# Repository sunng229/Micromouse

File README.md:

## Micromouse

An autonomous maze solving robot for the IEEE club at UCLA. The goal is to build and design a robot that autonomously navigates through a 16x16 maze to reach the center and back as fast as possible.

It accomplishes this using IR sensors to detect any walls, continously storing that data as it continues its path primarily using an algorithm called Floodfill, which is implemented in solver.c inside the Src folder.

Included are the following:
* Src folder: all the important source code  
* Inc folder: the H files for the C files
* the build/schematic files for the PCB

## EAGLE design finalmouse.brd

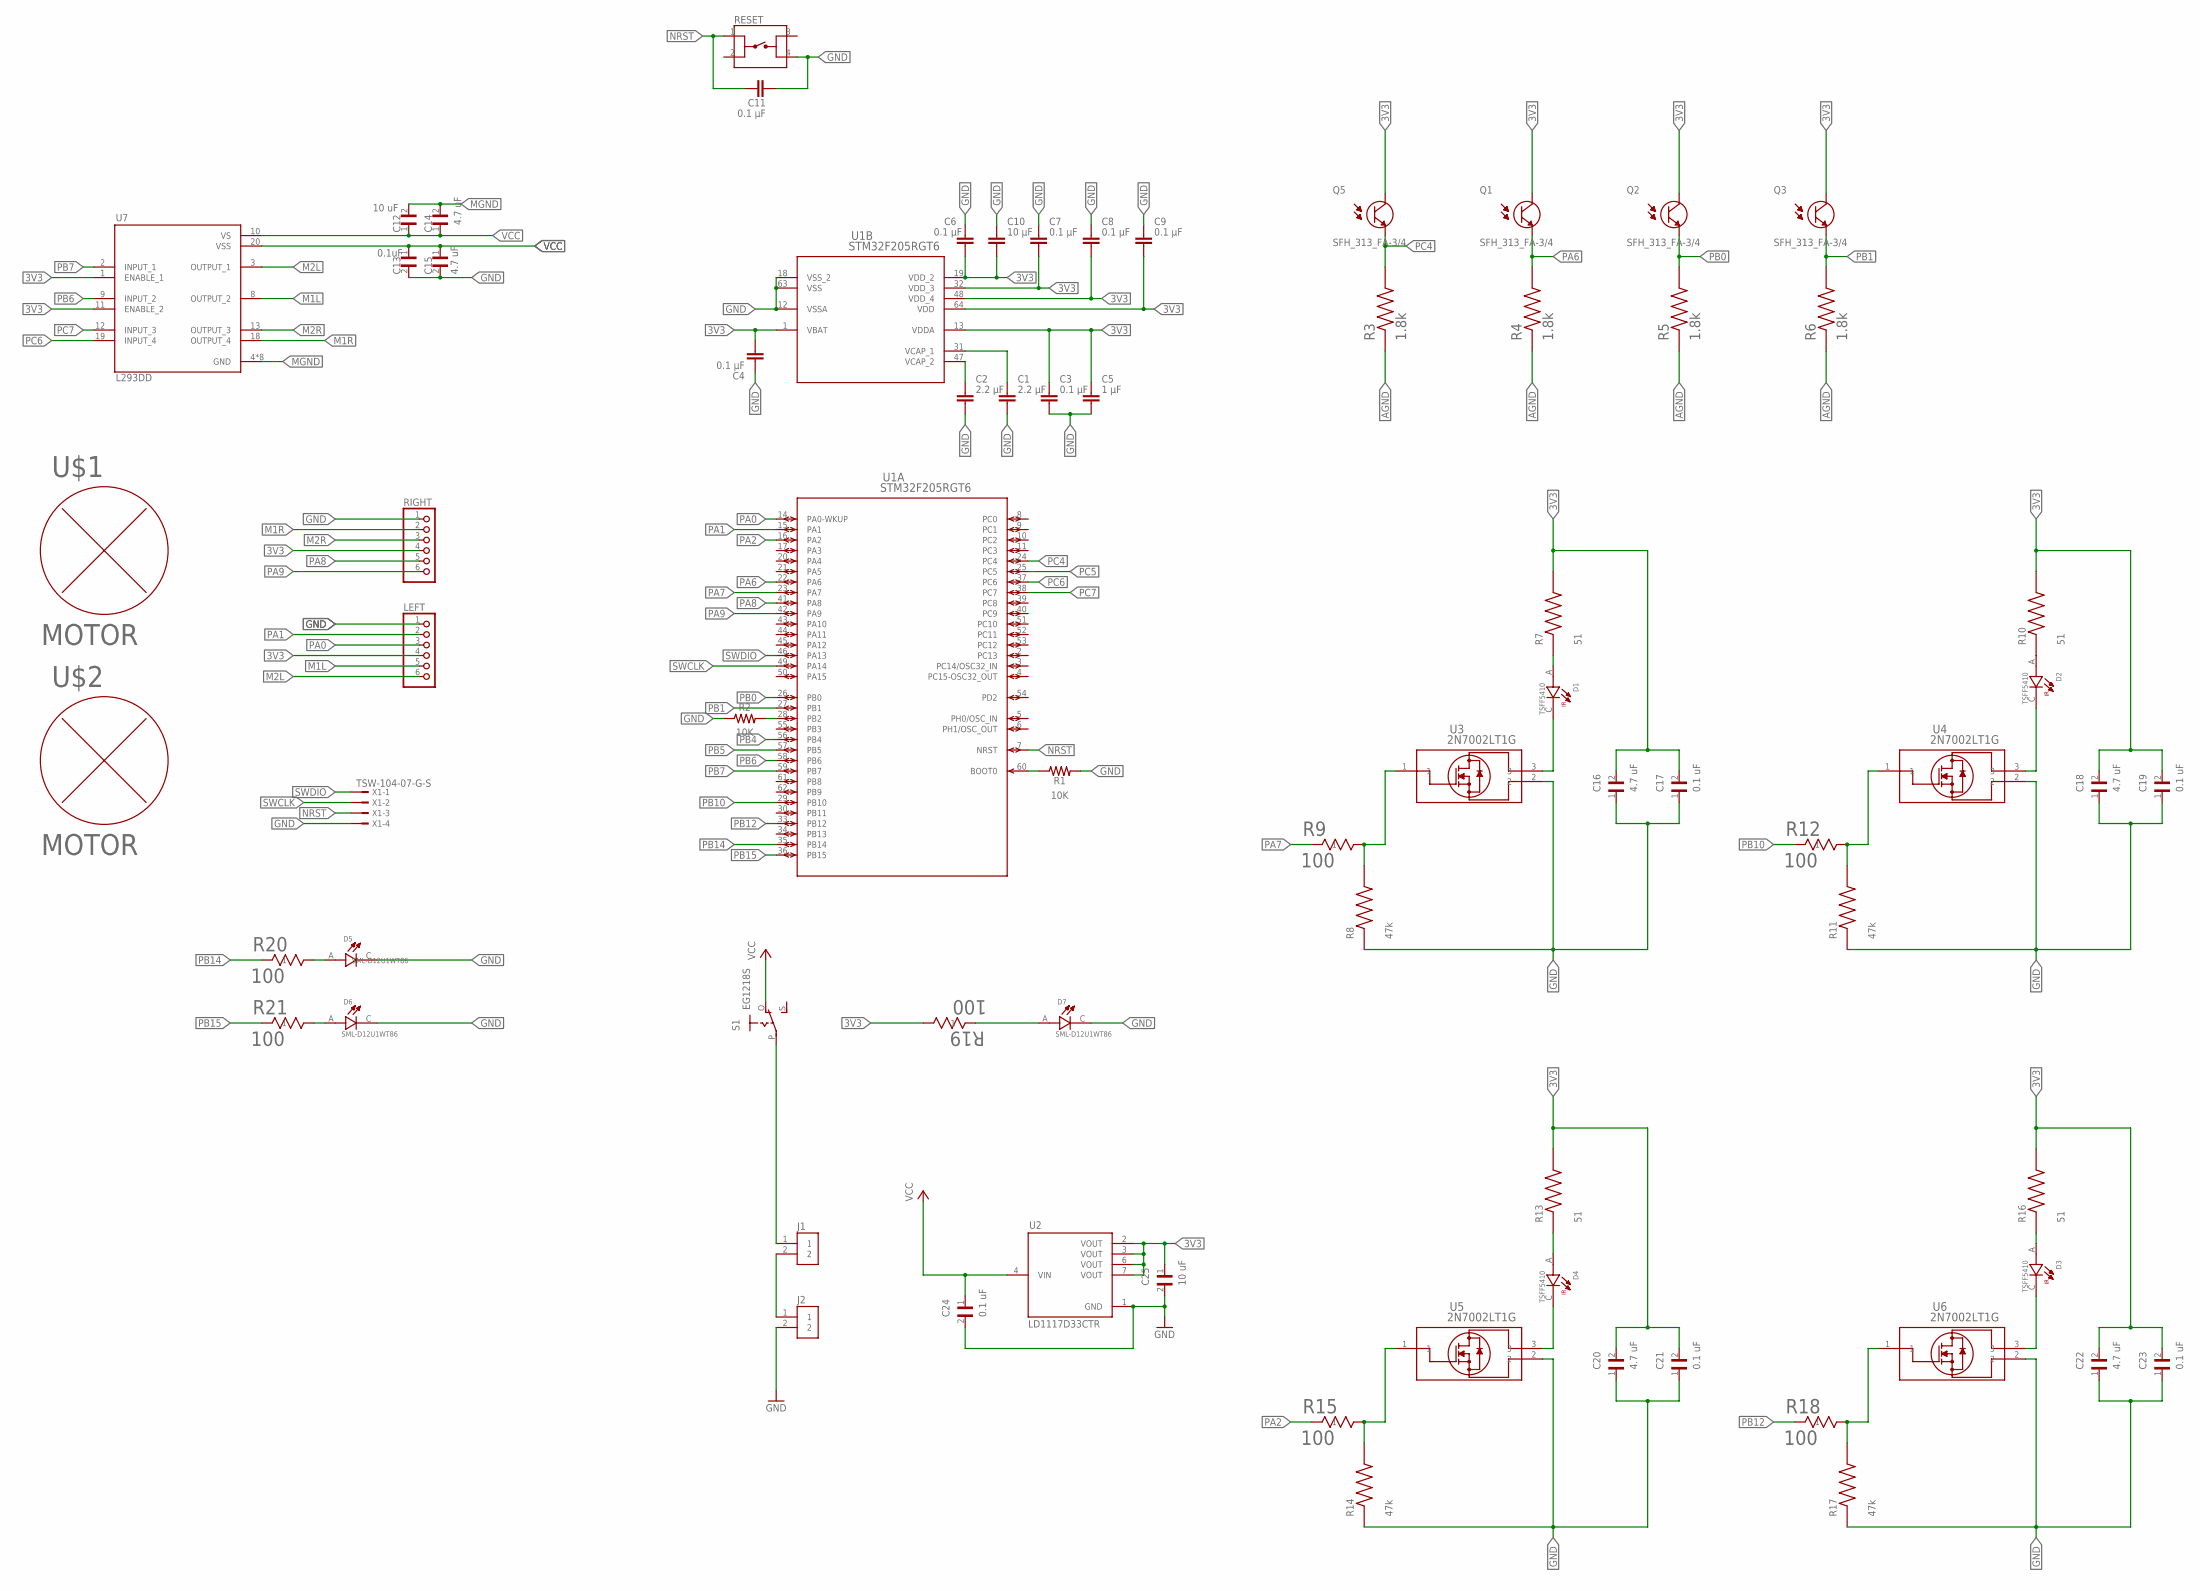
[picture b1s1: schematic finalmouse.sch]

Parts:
C1, C2: 2.2 μF; CAPC1608X85
C3, C4, C6, C7, C8, C9, C11: 0.1 μF; CAPC1608X85
C5: 1 μF; CAPC1608X85
C10: 10 μF; CAPC1608X85
C12, C25: 10 uF; CAPC2012X135N
C13: 0.1uF; CAPC2012X94N
C14, C15, C16, C18, C20, C22: 4.7 uF; CAPC2012X145N
C17, C19, C21, C23: 0.1 uF; CAPC2012X94N
C24: 0.1 uF; CAPC2012X135N
D1, D2, D3, D4: TSFF5410; LEDRD254W55D595H1160
D5, D6, D7: SML-D12U1WT86; LED_SML-D12Y1WT86
J1, J2: B2B-PH-K-S(LF)(SN); JST_B2B-PH-K-S(LF)(SN)
LEFT: PINHD-1X6; 1X06
Q1, Q2, Q3, Q5: SFH_313_FA-3/4; XDCR_SFH_313_FA-3/4
R1, R2: 10K; RESC1608X60
R3, R4, R5, R6: 1.8k; RESC2012X65N
R7, R10, R13, R16: 51; RES_ERJP06J510V
R8, R11, R14, R17: 47k; RES_ERA6ARB473V
R9, R12, R15, R18, R19, R20, R21: 100; RES_RK73G2A_KOA
RESET: FSM4JSMA; TE_FSM4JSMA
RIGHT: PINHD-1X6; 1X06
S1: EG1218S; EG1218
U1: STM32F205RGT6; LQFP64-10X10MM
U2: LD1117D33CTR; SOIC127P600X175-8N
U3, U4, U5, U6: 2N7002LT1G; SOT-23_3L_ONS
U7: L293DD; SOIC127P1032X265-20N
U$1, U$2: MOTOR
X1: TSW-104-07-G-S; TSW-104-XX-G-S

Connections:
3V3: C3.1, C4.2, C5.1, C6.2, C7.2, C8.2, C9.2, C10.2, C16.2, C17.2, C18.2, C19.2, C20.2, C21.2, C22.2, C23.2, C25.1, LEFT.4, Q1.2 (C), Q2.2 (C), Q3.2 (C), Q5.2 (C), R7.2, R10.2, R13.2, R16.2, R19.2, RIGHT.4, U1.1 (VBAT), U1.13 (VDDA), U1.19 (VDD_2), U1.32 (VDD_3), U1.48 (VDD_4), U1.64 (VDD), U2.2 (VOUT), U2.3 (VOUT), U2.6 (VOUT), U2.7 (VOUT), U7.1 (ENABLE_1), U7.11 (ENABLE_2)
AGND: R3.1, R4.1, R5.1, R6.1
GND: C1.2, C2.2, C3.2, C4.1, C5.2, C6.1, C7.1, C8.1, C9.1, C10.1, C11.2, C13.2, C15.2, C16.1, C17.1, C18.1, C19.1, C20.1, C21.1, C22.1, C23.1, C24.2, C25.2, D5.C, D6.C, D7.C, J2.2, LEFT.1, R1.2, R2.1, R8.1, R11.1, R14.1, R17.1, RESET.4, RIGHT.1, U1.12 (VSSA), U1.18 (VSS_2), U1.63 (VSS), U2.1 (GND), U3.2, U4.2, U5.2, U6.2, X1.4
M1L: LEFT.5, U7.8 (OUTPUT_2)
M1R: RIGHT.2, U7.18 (OUTPUT_4)
M2L: LEFT.6, U7.3 (OUTPUT_1)
M2R: RIGHT.3, U7.13 (OUTPUT_3)
MGND: C12.2, C14.2, U7.4 (GND), U7.5 (GND), U7.6 (GND), U7.7 (GND), U7.14 (GND), U7.15 (GND), U7.16 (GND), U7.17 (GND)
unnamed: C1.1, U1.31 (VCAP_1)
unnamed: C2.1, U1.47 (VCAP_2)
unnamed: R1.1, U1.60 (BOOT0)
unnamed: R2.2, U1.28 (PB2)
unnamed: J1.1, S1.P
unnamed: D1.A, R7.1
unnamed: R8.2, R9.2, U3.1
unnamed: D1.C, U3.3
unnamed: D2.A, R10.1
unnamed: R11.2, R12.2, U4.1
unnamed: D2.C, U4.3
unnamed: D3.A, R16.1
unnamed: R14.2, R15.2, U5.1
unnamed: D4.C, U5.3
unnamed: D4.A, R13.1
unnamed: R17.2, R18.2, U6.1
unnamed: D3.C, U6.3
unnamed: D7.A, R19.1
unnamed: J1.2, J2.1
unnamed: D5.A, R20.2
unnamed: D6.A, R21.2
NRST: C11.1, RESET.1, U1.7 (NRST), X1.3
PA0: LEFT.3, U1.14 (PA0-WKUP)
PA1: LEFT.2, U1.15 (PA1)
PA2: R15.1, U1.16 (PA2)
PA6: Q1.1 (E), R4.2, U1.22 (PA6)
PA7: R9.1, U1.23 (PA7)
PA8: RIGHT.5, U1.41 (PA8)
PA9: RIGHT.6, U1.42 (PA9)
PB0: Q2.1 (E), R5.2, U1.26 (PB0)
PB1: Q3.1 (E), R6.2, U1.27 (PB1)
PB4: U1.56 (PB4)
PB5: U1.57 (PB5)
PB6: U1.58 (PB6), U7.9 (INPUT_2)
PB7: U1.59 (PB7), U7.2 (INPUT_1)
PB10: R12.1, U1.29 (PB10)
PB12: R18.1, U1.33 (PB12)
PB14: R20.1, U1.35 (PB14)
PB15: R21.1, U1.36 (PB15)
PC4: Q5.1 (E), R3.2, U1.24 (PC4)
PC5: U1.25 (PC5)
PC6: U1.37 (PC6), U7.19 (INPUT_4)
PC7: U1.38 (PC7), U7.12 (INPUT_3)
SWCLK: U1.49 (PA14), X1.2
SWDIO: U1.46 (PA13), X1.1
VCC: C12.1, C13.1, C14.1, C15.1, C24.1, S1.O, U2.4 (VIN), U7.10 (VS), U7.20 (VSS)

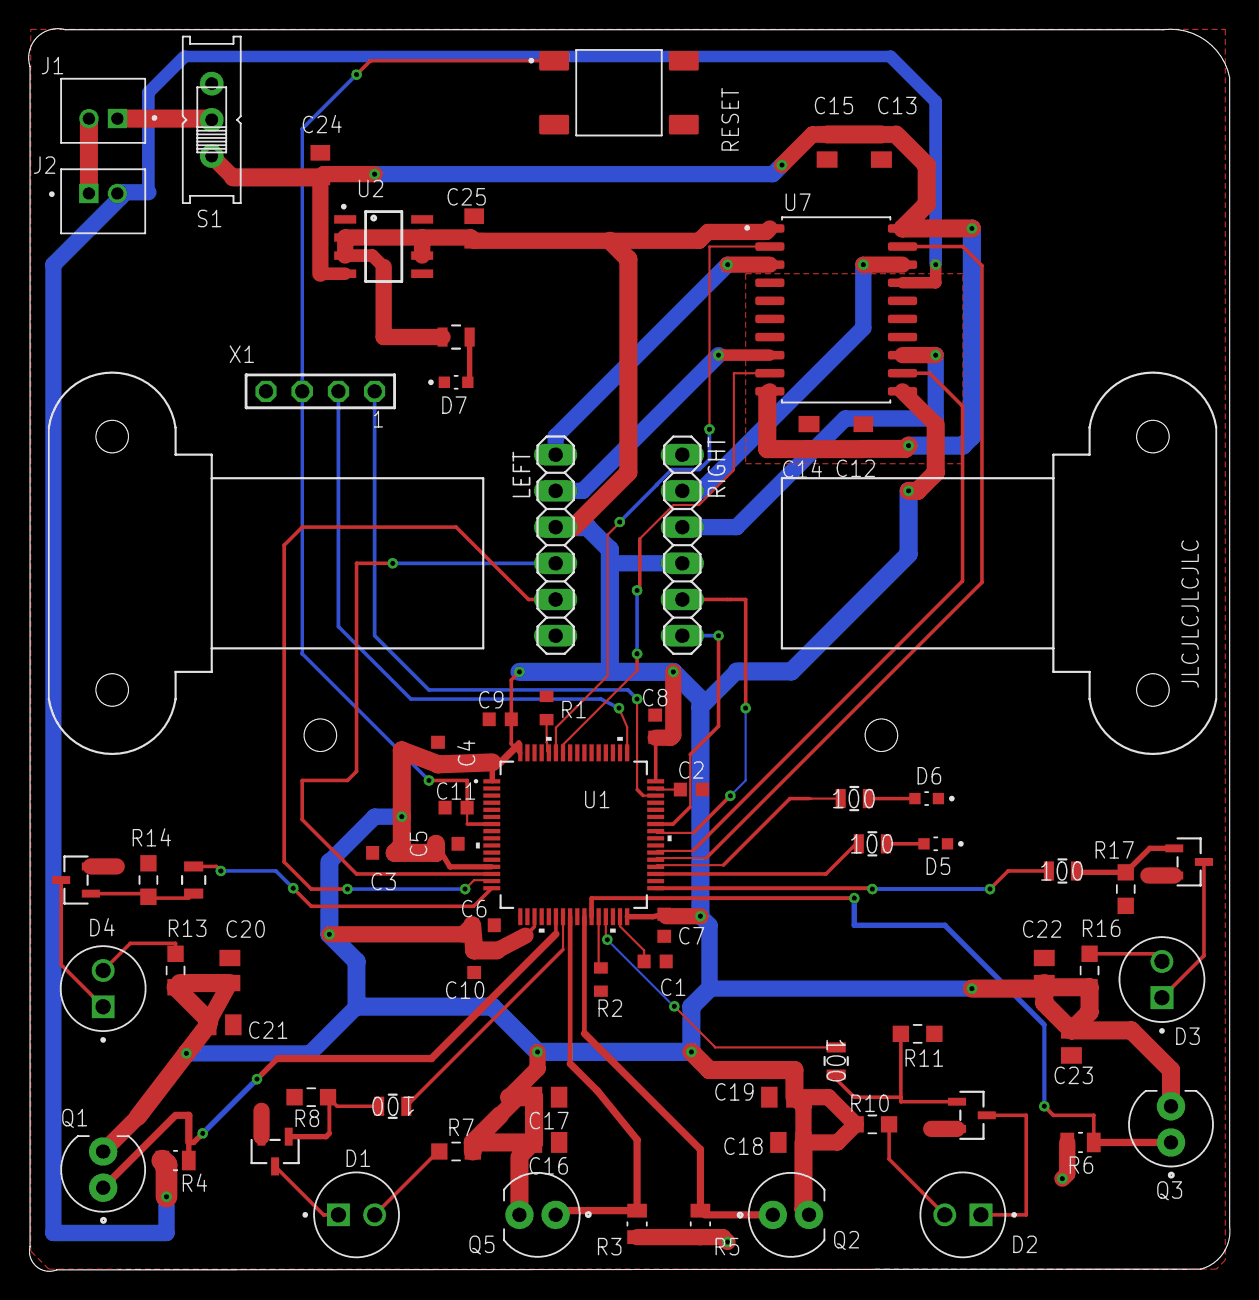
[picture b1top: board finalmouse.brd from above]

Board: 2 copper layers, 84.3 x 87.2 mm, 73 parts (0 on the bottom side), 51 nets.

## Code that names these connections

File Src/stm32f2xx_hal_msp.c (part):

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    __HAL_RCC_GPIOC_CLK_ENABLE();
    __HAL_RCC_GPIOB_CLK_ENABLE();
    /**ADC1 GPIO Configuration
    PA6     ------> ADC1_IN6
    PC4     ------> ADC1_IN14
    PB0     ------> ADC1_IN8
    PB1     ------> ADC1_IN9
    */
    GPIO_InitStruct.Pin = LeftReceiver_Pin;
    GPIO_InitStruct.Mode = GPIO_MODE_ANALOG;
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    __HAL_RCC_ADC1_CLK_DISABLE();

    /**ADC1 GPIO Configuration
    PA6     ------> ADC1_IN6
    PC4     ------> ADC1_IN14
    PB0     ------> ADC1_IN8
    PB1     ------> ADC1_IN9
    */
    HAL_GPIO_DeInit(LeftReceiver_GPIO_Port, LeftReceiver_Pin);

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
    __HAL_RCC_GPIOA_CLK_ENABLE();
    /**TIM1 GPIO Configuration
    PA8     ------> TIM1_CH1
    PA9     ------> TIM1_CH2
    */
    GPIO_InitStruct.Pin = RightEncoderCh1_Pin|RightEncoderCh2_Pin;
    GPIO_InitStruct.Mode = GPIO_MODE_AF_PP;
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
    __HAL_RCC_GPIOA_CLK_ENABLE();
    /**TIM2 GPIO Configuration
    PA0-WKUP     ------> TIM2_CH1
    PA1     ------> TIM2_CH2
    */
    GPIO_InitStruct.Pin = LeftEncoderCh1_Pin|LeftEnconderCh2_Pin;
    GPIO_InitStruct.Mode = GPIO_MODE_AF_PP;
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  /* USER CODE END TIM3_MspPostInit 0 */
    __HAL_RCC_GPIOC_CLK_ENABLE();
    /**TIM3 GPIO Configuration
    PC6     ------> TIM3_CH1
    PC7     ------> TIM3_CH2
    */
    GPIO_InitStruct.Pin = M1R_Pin|M2R_Pin;
    GPIO_InitStruct.Mode = GPIO_MODE_AF_PP;
    GPIO_InitStruct.Pull = GPIO_NOPULL;
    GPIO_InitStruct.Speed = GPIO_SPEED_FREQ_LOW;
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
    __HAL_RCC_GPIOB_CLK_ENABLE();
    /**TIM4 GPIO Configuration
    PB6     ------> TIM4_CH1
    PB7     ------> TIM4_CH2
    */
    GPIO_InitStruct.Pin = M1L_Pin|M2L_Pin;
    GPIO_InitStruct.Mode = GPIO_MODE_AF_PP;
    GPIO_InitStruct.Pull = GPIO_NOPULL;
    GPIO_InitStruct.Speed = GPIO_SPEED_FREQ_LOW;
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    __HAL_RCC_TIM1_CLK_DISABLE();

    /**TIM1 GPIO Configuration
    PA8     ------> TIM1_CH1
    PA9     ------> TIM1_CH2
    */
    HAL_GPIO_DeInit(GPIOA, RightEncoderCh1_Pin|RightEncoderCh2_Pin);

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    __HAL_RCC_TIM2_CLK_DISABLE();

    /**TIM2 GPIO Configuration
    PA0-WKUP     ------> TIM2_CH1
    PA1     ------> TIM2_CH2
    */
    HAL_GPIO_DeInit(GPIOA, LeftEncoderCh1_Pin|LeftEnconderCh2_Pin);

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

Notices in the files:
Src/stm32f2xx_hal_msp.c:
© Copyright (c) 2022 STMicroelectronics.
All rights reserved.
This software component is licensed by ST under BSD 3-Clause license,
the "License"; You may not use this file except in compliance with the
License. You may obtain a copy of the License at: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
(C) COPYRIGHT STMicroelectronics *****END OF FILE
parts and their libraries:
COPYRIGHT: Copyright (C) 2022 Ultra Librarian. All rights reserved.
COPYRIGHT: Copyright (C) 2021 Ultra Librarian. All rights reserved.
